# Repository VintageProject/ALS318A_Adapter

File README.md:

# ALS318A_Adapter
ALS318A to 2x 2364AS adapter for KIM Uno

This board allows to use a Russian ALS318A display to be used with the KIM Uno. It connects the 17-pin connector to a dual 2364AS footprint matching the KIM Uno board.
As the ALS318A is a common cathode type display, the KIM Uno software needs to be adjusted for use with CC displays, too.

Footprint position has been checked against the original KIM Uno board. 
Take care of pin clearances. Solder pins flush to board and use insulating layers if necessary.

Revision 00: Board outline matched to top of KIM Uno board. Might be bulky and interfere with power switch and other connectors.

Revision 01: Short board to match the size of the ALS318A board. Shouldn't interfere with other connectors.

Disclaimer: This is an untested training design. I won't be liable for any damage to your computer and/or electronics if you decide to use it. Use at your own risk.

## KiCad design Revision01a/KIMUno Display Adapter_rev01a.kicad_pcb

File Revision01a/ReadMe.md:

ALS318A to 2x 2364AS adapter for KIM Uno

This board allows to use a Russian ALS318A display to be used with the KIM Uno. It connects the 17-pin connector to a dual 2364AS footprint matching the KIM Uno board. As the ALS318A is a common cathode type display, the KIM Uno software needs to be adjusted for use with CC displays, too.

Footprint position has been checked against the original KIM Uno board. Board outline has been changed so that the adapter board has roughly the size of the ALS318A module. When soldering take care to leave enough room between the header pins and the Arduino pins.
Pin spacing has been changed to 2.5 mm for the ALS318A, and position was adjusted to centred.

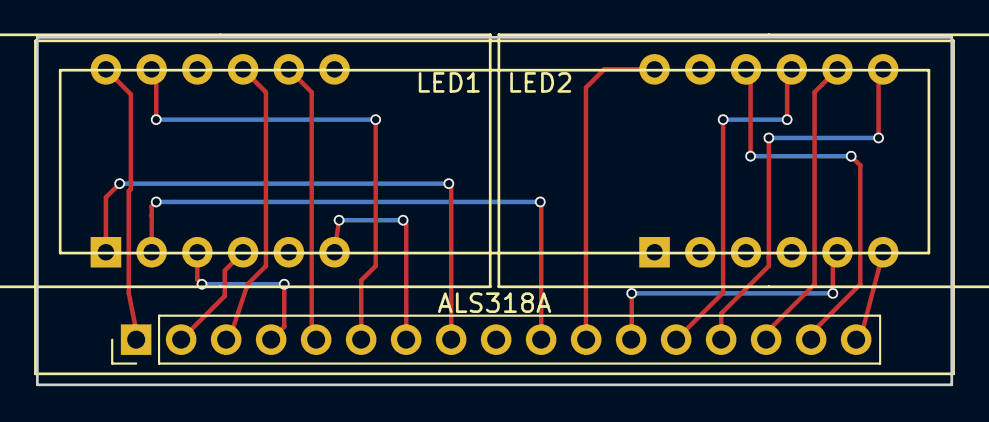
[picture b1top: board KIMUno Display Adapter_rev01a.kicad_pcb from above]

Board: 2 copper layers, 50.8 x 19.3 mm, 4 parts (0 on the bottom side), 16 nets.

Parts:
 : LOGO_VintageProject_B.SilkS
J1: ALS318A; ALS318A_BubbleLED_2.5mm
LED1, LED2: CC56-12; 3461AS-BS_4x7SEG-DIGIT_9mm

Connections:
/CC1: J1.1, LED1.12
/CC2: J1.3, LED1.9
/CC3: J1.5, LED1.8
/CC4: J1.7, LED1.6
/CC6: J1.11, LED2.12
/CC7: J1.13, LED2.9
/CC8: J1.15, LED2.8
/CC9: J1.17, LED2.6
/Seg_1a: J1.6, LED1.11
/Seg_1c: J1.2, LED1.4
/Seg_1d: J1.10, LED1.2
/Seg_1e: J1.8, LED1.1
/Seg_1h: J1.4, LED1.3
/Seg_2b: J1.14, LED2.7
/Seg_2f: J1.16, LED2.10
/Seg_2g: J1.12, LED2.5

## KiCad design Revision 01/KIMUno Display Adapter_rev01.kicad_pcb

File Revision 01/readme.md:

ALS318A to 2x 2364AS adapter for KIM Uno

This board allows to use a Russian ALS318A display to be used with the KIM Uno. It connects the 17-pin connector to a dual 2364AS footprint matching the KIM Uno board. As the ALS318A is a common cathode type display, the KIM Uno software needs to be adjusted for use with CC displays, too.

Footprint position has been checked against the original KIM Uno board.
Board outline has been changed so that the adapter board has roughly the size of the ALS318A module.
When soldering take care to leave enough room between the header pins and the Arduino pins.

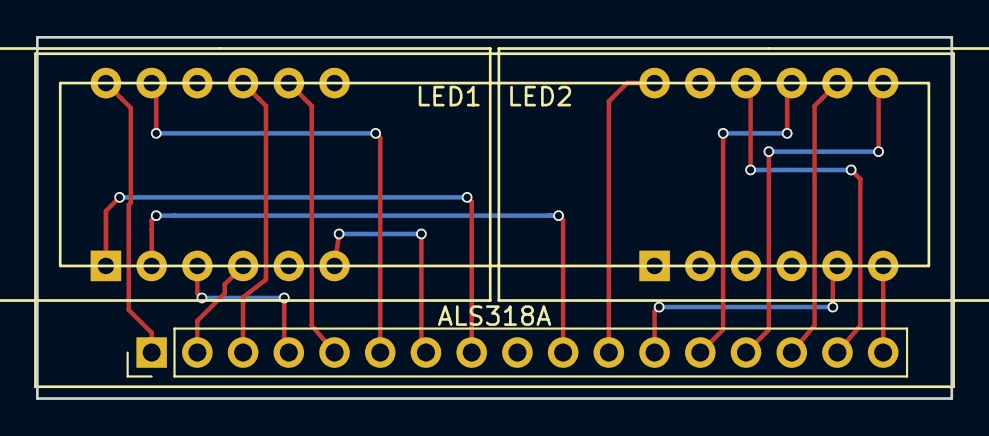
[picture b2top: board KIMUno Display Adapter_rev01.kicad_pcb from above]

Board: 2 copper layers, 50.8 x 20.1 mm, 4 parts (0 on the bottom side), 16 nets.

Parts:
 : ALS318A; ALS318A_BubbleLED
 #2: LOGO_VintageProject_B.SilkS
LED1, LED2: CC56-12; 3461AS-BS_4x7SEG-DIGIT_9mm

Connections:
/CC1: .1, LED1.12
/CC2: .3, LED1.9
/CC3: .5, LED1.8
/CC4: .7, LED1.6
/CC6: .11, LED2.12
/CC7: .13, LED2.9
/CC8: .15, LED2.8
/CC9: .17, LED2.6
/Seg_1a: .6, LED1.11
/Seg_1c: .2, LED1.4
/Seg_1d: .10, LED1.2
/Seg_1e: .8, LED1.1
/Seg_1h: .4, LED1.3
/Seg_2b: .14, LED2.7
/Seg_2f: .16, LED2.10
/Seg_2g: .12, LED2.5

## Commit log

2018-07-23 Rev. 00 - Initial commit
2018-07-23 OSHPark renders for reference
2018-07-23 Rev. 00 - Size adjustment
2018-07-23 Revision 01 - Short board
2018-07-23 Rename KIMUno Display Adapter.net to Revision 00/KIMUno Display Adapter.net
2018-07-23 Rename KIMUno Display Adapter.pro to Revision 00/KIMUno Display Adapter.pro
2018-07-23 Rename KIMUno Display Adapter.sch to Revision 00/KIMUno Display Adapter.sch
2018-07-23 Rename KIMUno Display Adapter.kicad_pcb to Revision 00/KIMUno Display Adapter.kicad_pcb
2018-07-23 Reupload Revision 00 - Long board for KIM Uno
2018-07-24 Several changes
    Redid the routing.
    Changed the LED footprint with smaller pads.
    Added logo to underside of the board.
2018-07-25 Rerouted tracks - Short Board for ALS318A
2018-09-24 New layout. Pin spacing corrected and display centred.
2018-09-24 ALS318A Footprint
    For you to play with. :-)
2018-09-24 Error with label visibility corrected
2018-09-24 Error with label visibility corrected.
